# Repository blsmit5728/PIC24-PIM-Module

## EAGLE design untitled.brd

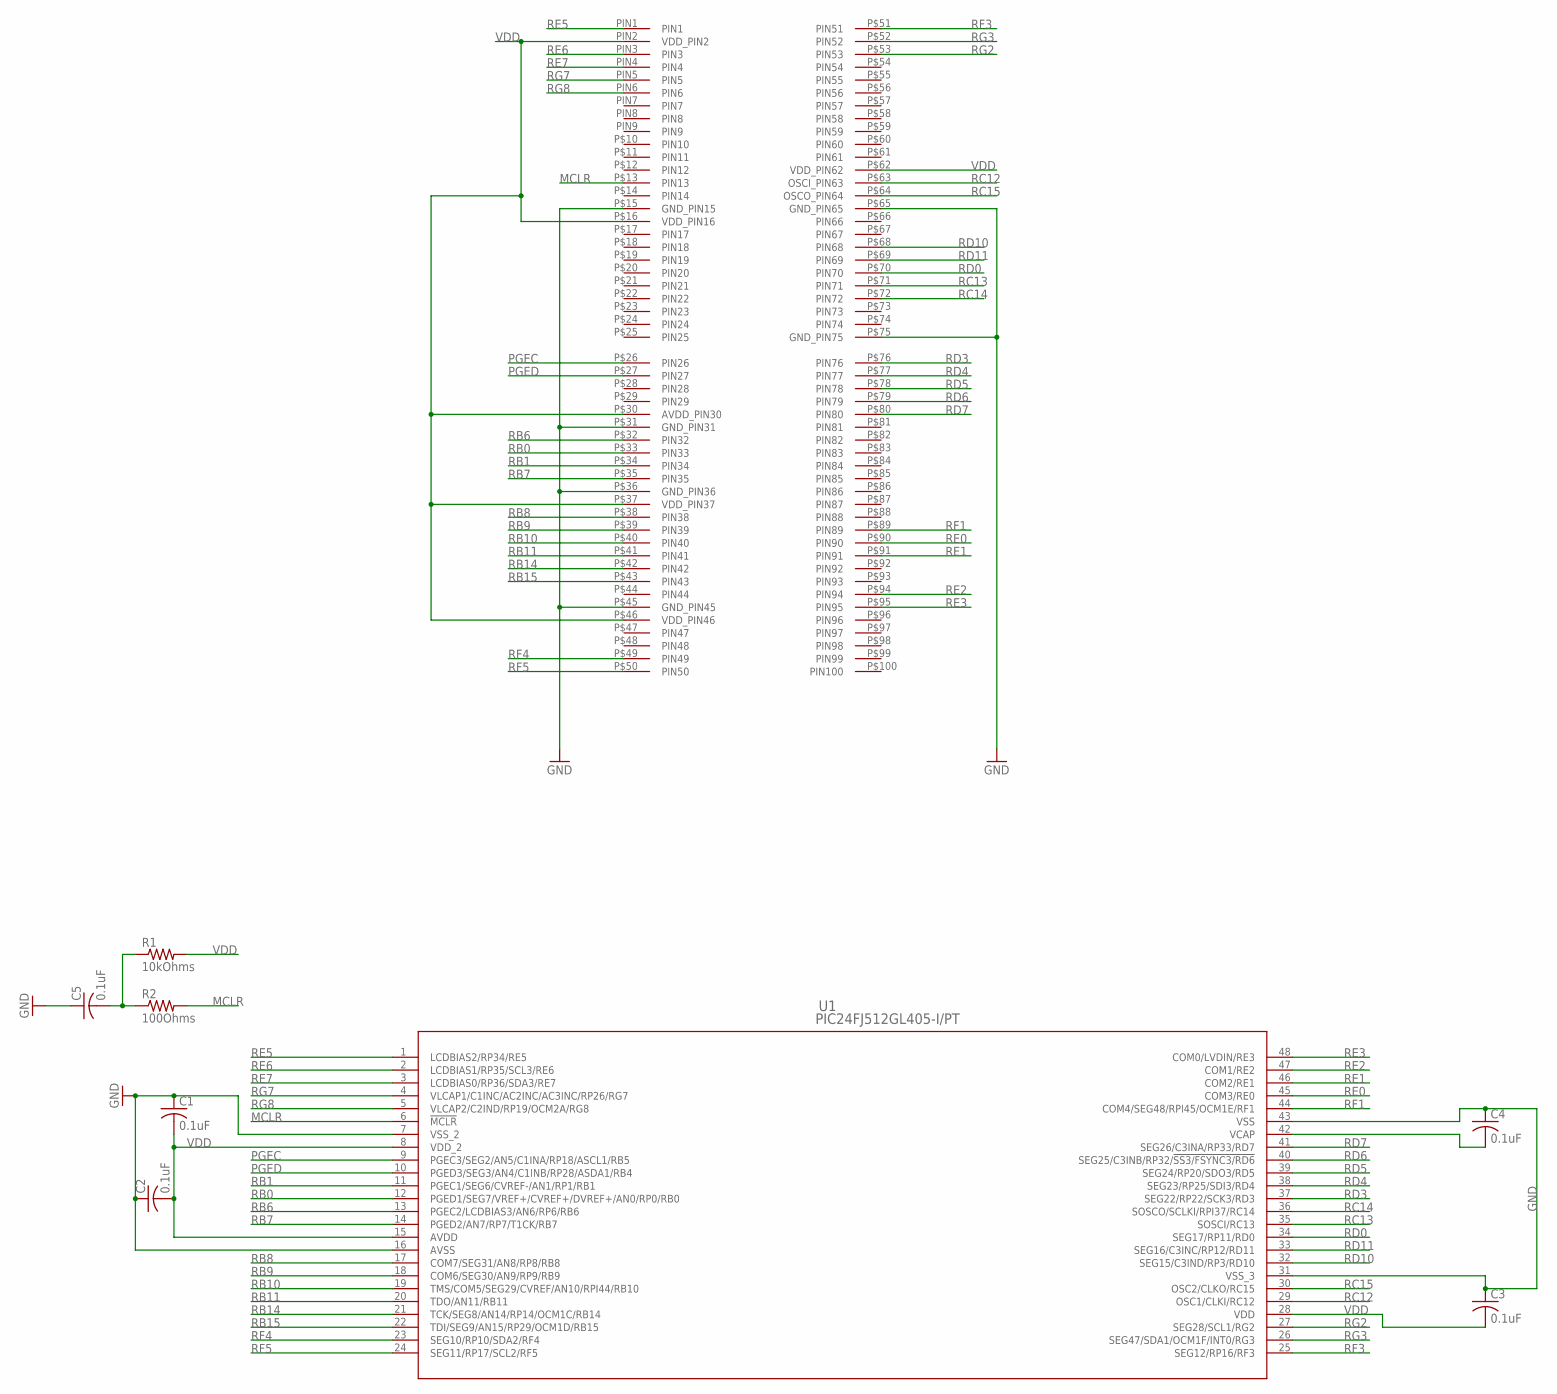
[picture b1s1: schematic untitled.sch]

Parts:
C1, C2, C3, C4, C5: 0.1uF; C0603
R1: 10kOhms; R0603
R2: 100Ohms; R0603
U1: PIC24FJ512GL405-I/PT; TQFP48_PT_MCH
U$1: PIC_24_PIM_100; PIC_PIM_100

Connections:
GND: C1.1, C2.1, C3.1, C4.1, C5.1, U1.7 (VSS_2), U1.16 (AVSS), U1.31 (VSS_3), U1.43 (VSS), U$1.P$15 (GND_PIN15), U$1.P$31 (GND_PIN31), U$1.P$36 (GND_PIN36), U$1.P$45 (GND_PIN45), U$1.P$65 (GND_PIN65), U$1.P$75 (GND_PIN75)
MCLR: R2.2, U1.6 (!MCLR), U$1.P$13 (PIN13)
unnamed: C5.2, R1.1, R2.1
unnamed: C4.2, U1.42 (VCAP)
PGEC: U1.9 (PGEC3/SEG2/AN5/C1INA/RP18/ASCL1/RB5), U$1.P$26 (PIN26)
PGED: U1.10 (PGED3/SEG3/AN4/C1INB/RP28/ASDA1/RB4), U$1.P$27 (PIN27)
RB0: U1.12 (PGED1/SEG7/VREF+/CVREF+/DVREF+/AN0/RP0/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), U$1.P$33 (PIN33)
RB1: U1.11 (PGEC1/SEG6/CVREF-/AN1/RP1/RB1), U$1.P$34 (PIN34)
RB6: U1.13 (PGEC2/LCDBIAS3/AN6/RP6/RB6), U$1.P$32 (PIN32)
RB7: U1.14 (PGED2/AN7/RP7/T1CK/RB7), U$1.P$35 (PIN35)
RB8: U1.17 (COM7/SEG31/AN8/RP8/RB8), U$1.P$38 (PIN38)
RB9: U1.18 (COM6/SEG30/AN9/RP9/RB9), U$1.P$39 (PIN39)
RB10: U1.19 (TMS/COM5/SEG29/CVREF/AN10/RPI44/RB10), U$1.P$40 (PIN40)
RB11: U1.20 (TDO/AN11/RB11), U$1.P$41 (PIN41)
RB14: U1.21 (TCK/SEG8/AN14/RP14/OCM1C/RB14), U$1.P$42 (PIN42)
RB15: U1.22 (TDI/SEG9/AN15/RP29/OCM1D/RB15), U$1.P$43 (PIN43)
RC12: U1.29 (OSC1/CLKI/RC12), U$1.P$63 (OSCI_PIN63)
RC13: U1.35 (SOSCI/RC13), U$1.P$71 (PIN71)
RC14: U1.36 (SOSCO/SCLKI/RPI37/RC14), U$1.P$72 (PIN72)
RC15: U1.30 (OSC2/CLKO/RC15), U$1.P$64 (OSCO_PIN64)
RD0: U1.34 (SEG17/RP11/RD0), U$1.P$70 (PIN70)
RD3: U1.37 (SEG22/RP22/SCK3/RD3), U$1.P$76 (PIN76)
RD4: U1.38 (SEG23/RP25/SDI3/RD4), U$1.P$77 (PIN77)
RD5: U1.39 (SEG24/RP20/SDO3/RD5), U$1.P$78 (PIN78)
RD6: U1.40 (SEG25/C3INB/RP32/!SS3/FSYNC3/RD6), U$1.P$79 (PIN79)
RD7: U1.41 (SEG26/C3INA/RP33/RD7), U$1.P$80 (PIN80)
RD10: U1.32 (SEG15/C3IND/RP3/RD10), U$1.P$68 (PIN68)
RD11: U1.33 (SEG16/C3INC/RP12/RD11), U$1.P$69 (PIN69)
RE0: U1.45 (COM3/RE0), U$1.P$90 (PIN90)
RE1: U1.46 (COM2/RE1), U$1.P$91 (PIN91)
RE2: U1.47 (COM1/RE2), U$1.P$94 (PIN94)
RE3: U1.48 (COM0/LVDIN/RE3), U$1.P$95 (PIN95)
RE5: U1.1 (LCDBIAS2/RP34/RE5), U$1.PIN1
RE6: U1.2 (LCDBIAS1/RP35/SCL3/RE6), U$1.PIN3
RE7: U1.3 (LCDBIAS0/RP36/SDA3/RE7), U$1.PIN4
RF1: U1.44 (COM4/SEG48/RPI45/OCM1E/RF1), U$1.P$89 (PIN89)
RF3: U1.25 (SEG12/RP16/RF3), U$1.P$51 (PIN51)
RF4: U1.23 (SEG10/RP10/SDA2/RF4), U$1.P$49 (PIN49)
RF5: U1.24 (SEG11/RP17/SCL2/RF5), U$1.P$50 (PIN50)
RG2: U1.27 (SEG28/SCL1/RG2), U$1.P$53 (PIN53)
RG3: U1.26 (SEG47/SDA1/OCM1F/INT0/RG3), U$1.P$52 (PIN52)
RG7: U1.4 (VLCAP1/C1INC/AC2INC/AC3INC/RP26/RG7), U$1.PIN5
RG8: U1.5 (VLCAP2/C2IND/RP19/OCM2A/RG8), U$1.PIN6
VDD: C1.2, C2.2, C3.2, R1.2, U1.8 (VDD_2), U1.15 (AVDD), U1.28 (VDD), U$1.P$16 (VDD_PIN16), U$1.P$30 (AVDD_PIN30), U$1.P$37 (VDD_PIN37), U$1.P$46 (VDD_PIN46), U$1.P$62 (VDD_PIN62), U$1.PIN2 (VDD_PIN2)

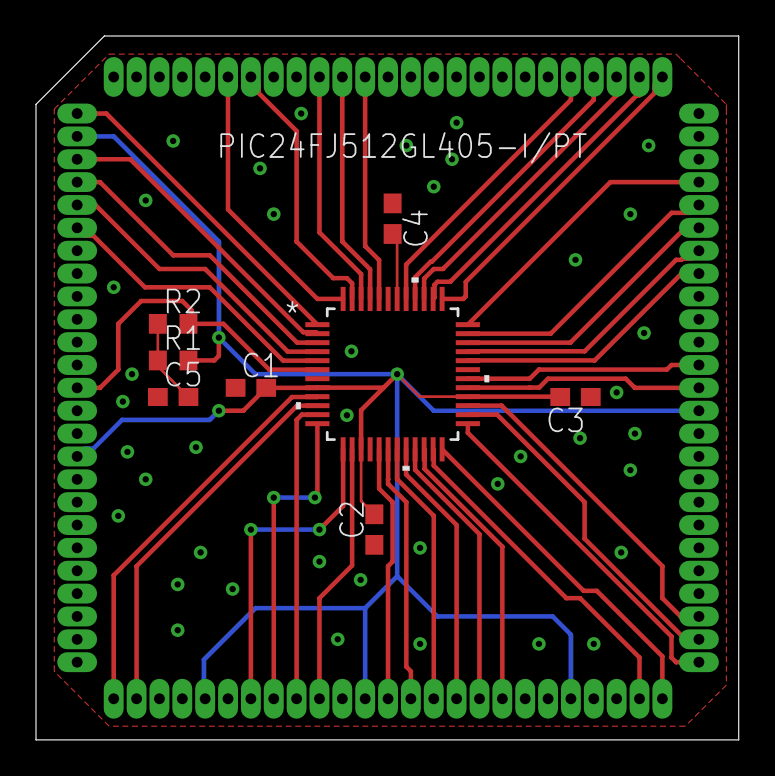
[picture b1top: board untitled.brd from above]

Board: 2 copper layers, 39.0 x 39.1 mm, 9 parts (0 on the bottom side), 44 nets.

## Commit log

2023-01-19 First
2023-01-19 Readme

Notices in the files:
parts and their libraries:
COPYRIGHT: Copyright (C) 2023 Ultra Librarian. All rights reserved.
